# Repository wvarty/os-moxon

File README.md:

# os-moxon
Open source PCB based Moxon antenna

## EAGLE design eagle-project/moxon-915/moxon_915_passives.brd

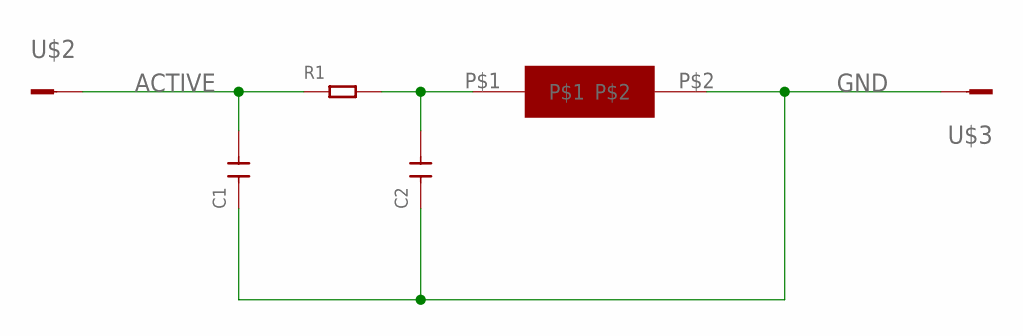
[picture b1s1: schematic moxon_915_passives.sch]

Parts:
C1, C2: 1uf; C0805
R1: 1K; R0805
U$1: MOXON-915MOX1; MOXON-915
U$2, U$3: CONN-1PAD2; PAD2

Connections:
ACTIVE: C1.2, R1.1, U$2.P$1
GND: C1.1, C2.1, U$1.P$2, U$3.P$1
unnamed: C2.2, R1.2, U$1.P$1

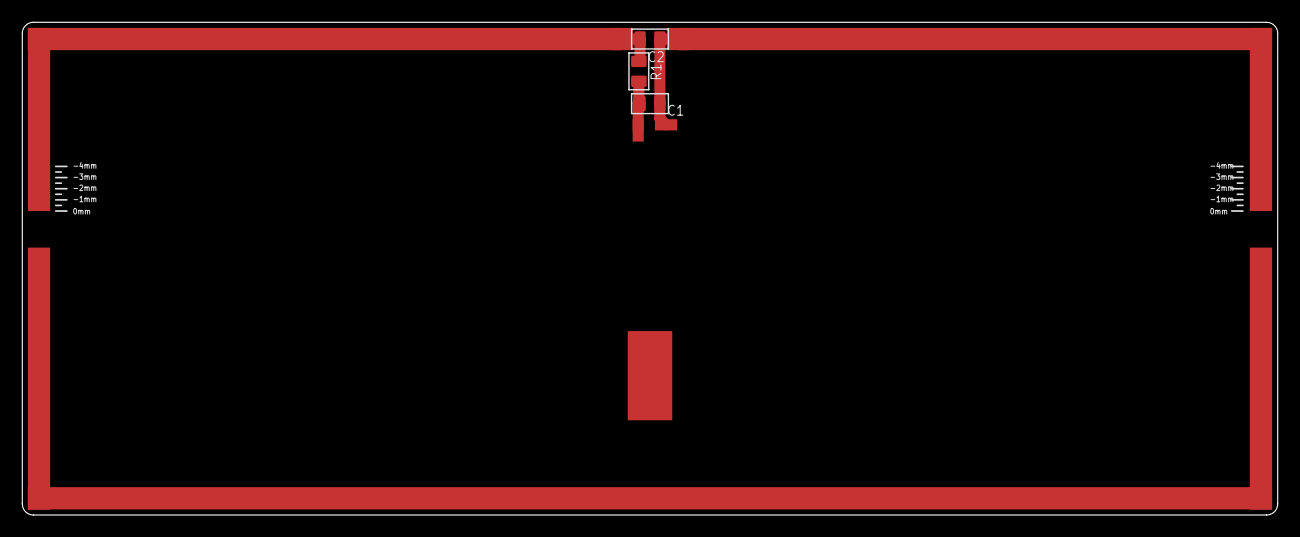
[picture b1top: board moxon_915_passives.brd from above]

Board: 2 copper layers, 112.6 x 44.2 mm, 6 parts (0 on the bottom side), 3 nets.

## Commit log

2020-04-30 Added gerbers for v1
